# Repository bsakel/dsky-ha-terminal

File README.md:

# DSKY Home Assistant terminal

An Apollo Guidance Computer DSKY lookalike that works as a Home Assistant control terminal. It has:

- a **Raspberry Pi Zero 2 W** with a 4.0" 800×480 touch screen in the display window: a **FYSETC CTP40** (a HyperPixel 4.0 clone; the model and BOM still show the HyperPixel, see *Pending steps*);
- 19 **Gateron low-profile** keys;
- 10 RGB **status lights**, driven by an **RP2040-Zero** that appears to the Pi as a USB device.

The mechanical design is based on [MKme/AGC_DSKY_Replica](https://github.com/MKme/AGC_DSKY_Replica) (GPL-3.0). The main case and rear cover are dropped, the mid frame is split for support-free printing, and the electronics are new.

The STEP model of the original replica, with its lenses and original electronics, isn't in this repo. It's offered upstream instead, as `3D Models/DSKY_Original_Build.step`:

- the pull request: [MKme/AGC_DSKY_Replica#2](https://github.com/MKme/AGC_DSKY_Replica/pull/2), "Create a step file with the complete assembly";
- the fork it comes from: [bsakel/AGC_DSKY_Replica](https://github.com/bsakel/AGC_DSKY_Replica), [`3D Models/DSKY_Original_Build.step`](https://github.com/bsakel/AGC_DSKY_Replica/blob/master/3D%20Models/DSKY_Original_Build.step).

## Repository layout

```
hardware/
  BOM.md                    full bill of materials (printed parts, fasteners, electronics)
  cad/
    DSKY_HA_Terminal.step   this build: both options in one file as selectable components
                            (the original replica's STEP lives upstream, see above)
  pcb/                      Option A: KiCad projects, panel, JLCPCB BOM/CPL (see pcb/README.md)
  diy/                      Option B: hand-wired schematic (KiCad) + wiring diagram
firmware/                   RP2040-Zero firmware (keys + status lights)  - to do
software/                   Pi side: Home Assistant UI / bridge          - to do
docs/img/                   renders
```

## Two ways to build it

| | Option A – Custom PCBs | Option B – Hand-wired |
|---|---|---|
| Keys | Hot-swap sockets on a factory-assembled PCB | Switches wired point-to-point with 1N4148 diodes |
| Status lights | WS2812B on a PCB behind the splitter | 10 WS2812B mini boards in a printed holder |
| You solder | 19 sockets, RP2040-Zero, 2 connectors | Everything |
| Firmware | same | same |

Both options use the same matrix and pins, so one firmware covers both builds:

- **Rows:** GP28, GP29, GP15.
- **Columns:** GP9–GP13, GP26, GP27.
- **LED data:** GP14.

In `DSKY_HA_Terminal.step` the top-level components *Option A – Custom PCBs* and *Option B – Hand-wired* hold the parts that differ between the builds. Hide one of them in Fusion 360 to see the other build.

## Status

**Work in progress, parked.** The hardware is designed and passes KiCad DRC. Nothing has been ordered or built yet, and the firmware and software haven't been started.

- [x] 3D model (both options), printable parts, fasteners
- [x] PCBs designed, routed and panelised; JLCPCB BOM/CPL
- [x] Hand-wired schematic
- [x] KiCad DRC and ERC on both boards, the panel and the DIY schematic: no errors (warnings only, listed below)
- [ ] Footprint check against real parts, then order
- [ ] 3D model updated for the CTP40 screen and the final keyboard PCB
- [ ] Firmware
- [ ] Home Assistant software

## Pending steps

Work through these in order; each group builds on the one before.

### 1. PCBs (before ordering)

1. **Print the keyboard board 1:1** and lay a real Gateron LP switch, hot-swap socket and RP2040-Zero on it.
2. **Gateron_LP_Hotswap footprint.** Its back-side courtyard (x −9.75…8.0, y 2.0…8.3) was estimated from the pad positions. Check it against the socket datasheet.
3. **RP2040-Zero footprint.** The copy on the keyboard board differs from the one in `lib/dsky.pretty`. Compare both with the Waveshare drawing, then keep the correct one in both places.
4. **3D viewer (Alt+3)** in KiCad: check that the sockets and RP2040 sit on the back and the LEDs on the front.
5. **Optional clean-ups** (all DRC warnings, none block ordering):
   - Net names differ between schematic and board (`/+5V` vs `+5V`, 235 parity warnings). It comes from the generator's labels; "Update PCB from schematic" would rename every net.
   - Add no-connect flags to the unused RP2040 pins and the last LED's DOUT (the ERC errors).
   - Silkscreen overlaps and clipping, the missing `MPN` field, `MouseBite_0.5` missing from the library.
6. **Order.** Follow `hardware/pcb/README.md`: Gerbers plus the BOM/CPL files from `pcb/jlcpcb/panel/`. Check the rotation of every part in JLCPCB's placement preview (WS2812B notch, diode bands).

### 2. Mechanical (3D model, in Fusion 360)

1. **Swap the HyperPixel for the CTP40** ([FYSETC/FYSETC-CTP40](https://github.com/FYSETC/FYSETC-CTP40)):
   - The CTP40's active area sits about 1.5 mm further along the long axis than the HyperPixel's, relative to the mounting holes. Move the two display-housing holes by that much (confirm against the FYSETC drawing first).
   - The CTP40's thickness isn't published. Measure it; the model allows 4.0 mm from the back of the board to the front of the glass.
   - Rename the "(HyperPixel)" parts here and in `hardware/BOM.md`.
2. **Keyboard PCB model:** update it to the KiCad board. It still has the old MX-style holes and lacks the RP2040 tab.
3. **Spacers:** the keyboard spacers are Ø6.5 mm. The PCB courtyards now allow for that (r 3.5 on the back), so keep them that size or smaller.
4. **Upstream PR.** Follow up on [MKme/AGC_DSKY_Replica#2](https://github.com/MKme/AGC_DSKY_Replica/pull/2), the original-build STEP file. Once it's merged, point the links above at MKme's repo instead of the fork.
5. Export the STLs (see `hardware/BOM.md`).

### 3. Firmware (RP2040-Zero)

Decisions to make first, one at a time:

1. **Stack:** CircuitPython, MicroPython, Arduino-Pico or KMK/QMK.
2. **Pi ↔ RP2040 protocol:** USB CDC serial, HID + serial, or something else. Key events go up to the Pi; lamp states come down.
3. **LED brightness limit:** all 10 LEDs at full white draw about 600 mA from the Pi's USB port, so the firmware must cap it.

Pins, matrix and LED order are in `firmware/README.md`.

### 4. Software (Pi Zero 2 W)

1. **CTP40 driver:** FYSETC ships Pi 3/Pi 4 overlays. Check what works on the current Raspberry Pi OS on the Zero 2 W.
2. **UI:** a kiosk browser (for example a Home Assistant dashboard) or a native app.
3. **VERB/NOUN mapping:** design how DSKY-style VERB/NOUN entries map to Home Assistant services.

### Notes for picking this up again

- **KiCad version.** The projects are KiCad 8 format. KiCad 10 opens them, but saving converts the files to the new format. Decide whether to upgrade before you edit and save in KiCad 10.
- **Generators.** `hardware/pcb/scripts/` generates the boards. Regenerating overwrites every hand edit, so prefer small targeted patches.
- **Python.** Python isn't on the PATH on the dev machine. KiCad's bundled Python works (it includes numpy): `"C:\Program Files\KiCad\10.0\bin\python.exe"`.
- **DRC from the command line.** This runs without saving the board:

  ```bash
  kicad-cli pcb drc --refill-zones --schematic-parity --severity-all -o drc.rpt hardware/pcb/keyboard-board/keyboard_board.kicad_pcb
  ```

  Use the same command for the status board, and drop `--schematic-parity` for the panel.

## Licence

GPL-3.0, inherited from the original AGC_DSKY_Replica project. See `LICENSE`.

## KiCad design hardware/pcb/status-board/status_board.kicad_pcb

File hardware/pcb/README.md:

# Custom PCBs (Option A)

| Folder | What it is |
|---|---|
| `keyboard-board/` | 168 × 77 mm board with 19 Gateron LP hot-swap sockets, a diode per key and the RP2040-Zero on the back. |
| `status-board/` | 60 × 106 mm board with 10 WS2812B LEDs behind the status lenses. |
| `panel/` | Both boards in one 230 × 106 mm panel joined by two mouse-bite tabs. This is the file you order. |
| `lib/` | Project symbol and footprint libraries, used by all three projects through `${KIPRJMOD}/../lib`. |
| `jlcpcb/` | BOM and CPL (pick-and-place) files for JLCPCB assembly, one set per project. |
| `scripts/` | The Python generators that produced the boards. Only needed if you want to regenerate them. |

Both boards were routed and checked with the generator's own clearance and connectivity checks:

- 0.2 mm copper clearance and 0.4 mm to the board edge.
- No errors and no unconnected nets.

KiCad's DRC is still the final word.

## Before ordering (KiCad 8)

1. **Check the footprints against real parts.**
   - Open `lib/dsky.pretty` in the footprint editor.
   - **Gateron_LP_Hotswap.** Check it against your socket's datasheet: the centre hole is 5.1 mm, the two pin holes are 3.0 mm, and the pads are on the back. Print the board 1:1 on paper and lay a switch on it.
   - **RP2040-Zero.** Check the pad pitch and pin names against the Waveshare drawing. The module is soldered to the back by its castellated edge, with the USB-C pointing up out of the tab.
2. **Open each board.** Open `keyboard-board/keyboard_board.kicad_pro` and `status-board/status_board.kicad_pro`.
   - Press **B** to fill the zones. The GND pour on the back layer is defined but not filled.
   - Run **Inspect → Design Rules Checker** with *Test for parity between PCB and schematic* enabled.
   - Fix or accept anything it reports. Silkscreen-over-pad warnings are cosmetic.
3. **Open the panel.** Open `panel/dsky_panel.kicad_pcb`, fill the zones (B) and run DRC.
   - The panel has no schematic, so turn off schematic parity.
   - Nets carry a `K_` prefix (keyboard) or `S_` prefix (status), and status-board references are numbered from 100 so that they don't clash.
4. **Make the Gerbers.** Use *File → Fabrication Outputs → Gerbers* with JLCPCB's recommended settings, plus the drill files. Alternatively, install the **Fabrication Toolkit** plugin, which builds Gerbers, BOM and CPL in one click.
5. **Upload to JLCPCB.**
   - Board settings: 2 layers, 1.6 mm, HASL lead-free or ENIG, any colour.
   - **Assembly:** PCBA, top side. Upload `jlcpcb/panel/dsky_panel_BOM.csv` and `dsky_panel_CPL.csv`.
   - In the placement preview, **check the rotation of every part type**, especially the WS2812B LEDs: the notch (pin 1, VDD) must sit at the marked corner. The diode band must face the cathode mark. Rotate any part that is off in the preview; JLC applies your correction.
   - The hot-swap sockets, RP2040-Zero and connectors are marked *do not populate*. They are deliberately missing from the BOM, so JLC will not ask about them.

## Panel or separate boards?

JLCPCB treats a file containing several designs as a panel and may add a small "multiple designs" fee. Compare two quotes:

1. **The panel.** One board of 230 × 106 mm and one assembly setup.
2. **Two separate orders.** Two boards under 100 × 100 / 170 mm and two setups.

Assembly setup and extended-part fees usually make the panel the cheaper option. If they don't, the individual projects are ready to order on their own with their own BOM/CPL.

After delivery, snap the panel apart at the two mouse-bite tabs (pliers, then file the nubs flat).

## Hand assembly after delivery

1. **Hot-swap sockets** (back side): 19 of them, two pads each. Tin one pad, place the socket, then solder both pads.
2. **RP2040-Zero** (back side): line up the castellations with the pads and solder only the pins that are used. Those are 5V, GND, GP9–GP15 and GP26–GP29; soldering all of them is fine too.
3. **Status cable**, between J1 on the keyboard board and J101 (J1 on its own board) on the status board:
   - Pin 1: +5V
   - Pin 2: DIN
   - Pin 3: GND

## Pin map (same for both builds)

| Function | RP2040 GPIO |
|---|---|
| ROW0 (VERB, +, 7, 8, 9, CLR, ENTR) | GP28 |
| ROW1 (NOUN, −, 4, 5, 6, PRO, RSET) | GP29 |
| ROW2 (0, 1, 2, 3, KEY REL) | GP15 |
| COL0 … COL6 | GP9, GP10, GP11, GP12, GP13, GP26, GP27 |
| WS2812B data | GP14 (buffered to 5 V on Option A) |

The diodes go column → row (COL2ROW).

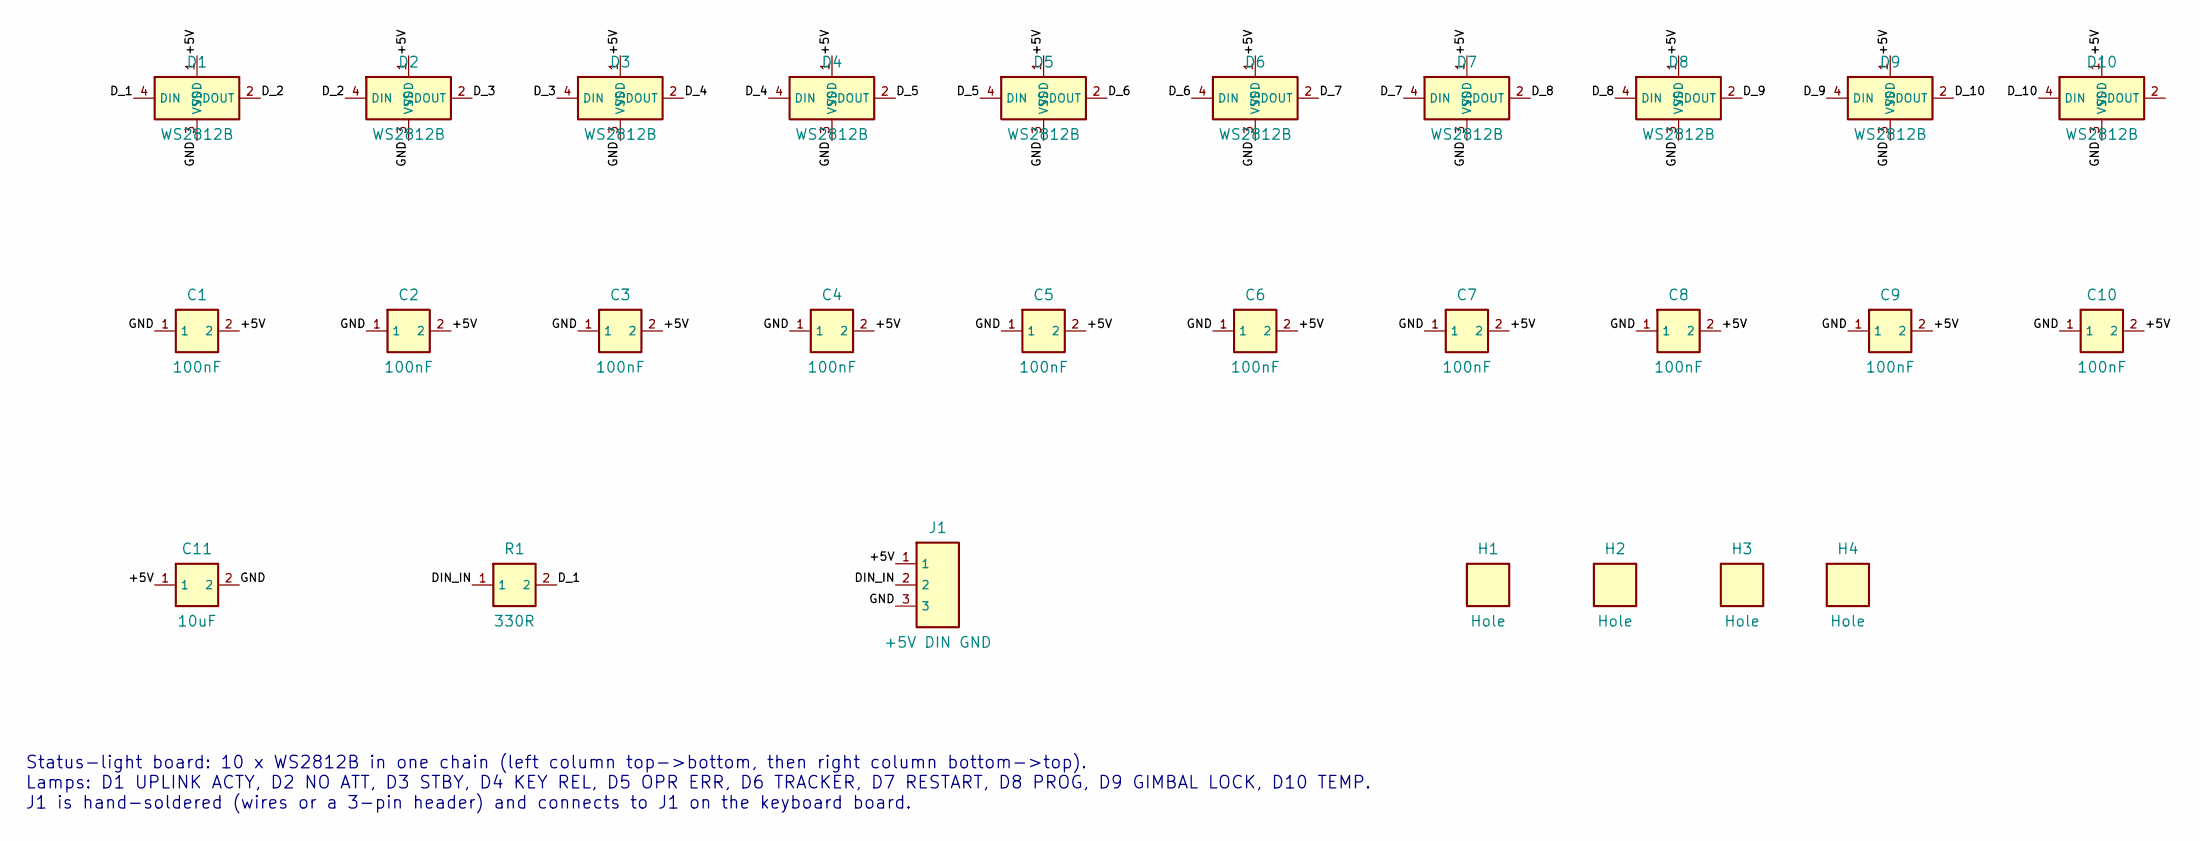
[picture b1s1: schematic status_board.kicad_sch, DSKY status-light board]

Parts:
C1, C2, C3, C4, C5, C6, C7, C8, C9, C10: 100nF; C_0603; MPN CC0603KRX7R9BB104; LCSC C14663
C11: 10uF; C_0805; MPN CL21A106KAYNNNE; LCSC C15850
D1, D2, D3, D4, D5, D6, D7, D8, D9, D10: WS2812B; WS2812B_5050; MPN WS2812B-B/T; LCSC C2761795
H1, H2, H3, H4: Hole; Hole_2.2
J1: +5V DIN GND; Conn_1x03_P2.54
R1: 330R; R_0603; MPN 0603WAF3300T5E; LCSC C23138

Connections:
+5V: C1.2, C2.2, C3.2, C4.2, C5.2, C6.2, C7.2, C8.2, C9.2, C10.2, C11.1, D1.1 (VDD), D2.1 (VDD), D3.1 (VDD), D4.1 (VDD), D5.1 (VDD), D6.1 (VDD), D7.1 (VDD), D8.1 (VDD), D9.1 (VDD), D10.1 (VDD), J1.1
DIN_IN: J1.2, R1.1
D_1: D1.4 (DIN), R1.2
D_2: D1.2 (DOUT), D2.4 (DIN)
D_3: D2.2 (DOUT), D3.4 (DIN)
D_4: D3.2 (DOUT), D4.4 (DIN)
D_5: D4.2 (DOUT), D5.4 (DIN)
D_6: D5.2 (DOUT), D6.4 (DIN)
D_7: D6.2 (DOUT), D7.4 (DIN)
D_8: D7.2 (DOUT), D8.4 (DIN)
D_9: D8.2 (DOUT), D9.4 (DIN)
D_10: D9.2 (DOUT), D10.4 (DIN)
GND: C1.1, C2.1, C3.1, C4.1, C5.1, C6.1, C7.1, C8.1, C9.1, C10.1, C11.2, D1.3 (VSS), D2.3 (VSS), D3.3 (VSS), D4.3 (VSS), D5.3 (VSS), D6.3 (VSS), D7.3 (VSS), D8.3 (VSS), D9.3 (VSS), D10.3 (VSS), J1.3

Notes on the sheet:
Status-light board: 10 x WS2812B in one chain (left column top->bottom, then right column bottom->top). Lamps: D1 UPLINK ACTY, D2 NO ATT, D3 STBY, D4 KEY REL, D5 OPR ERR, D6 TRACKER, D7 RESTART, D8 PROG, D9 GIMBAL LOCK, D10 TEMP. J1 is hand-soldered (wires or a 3-pin header) and connects to J1 on t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

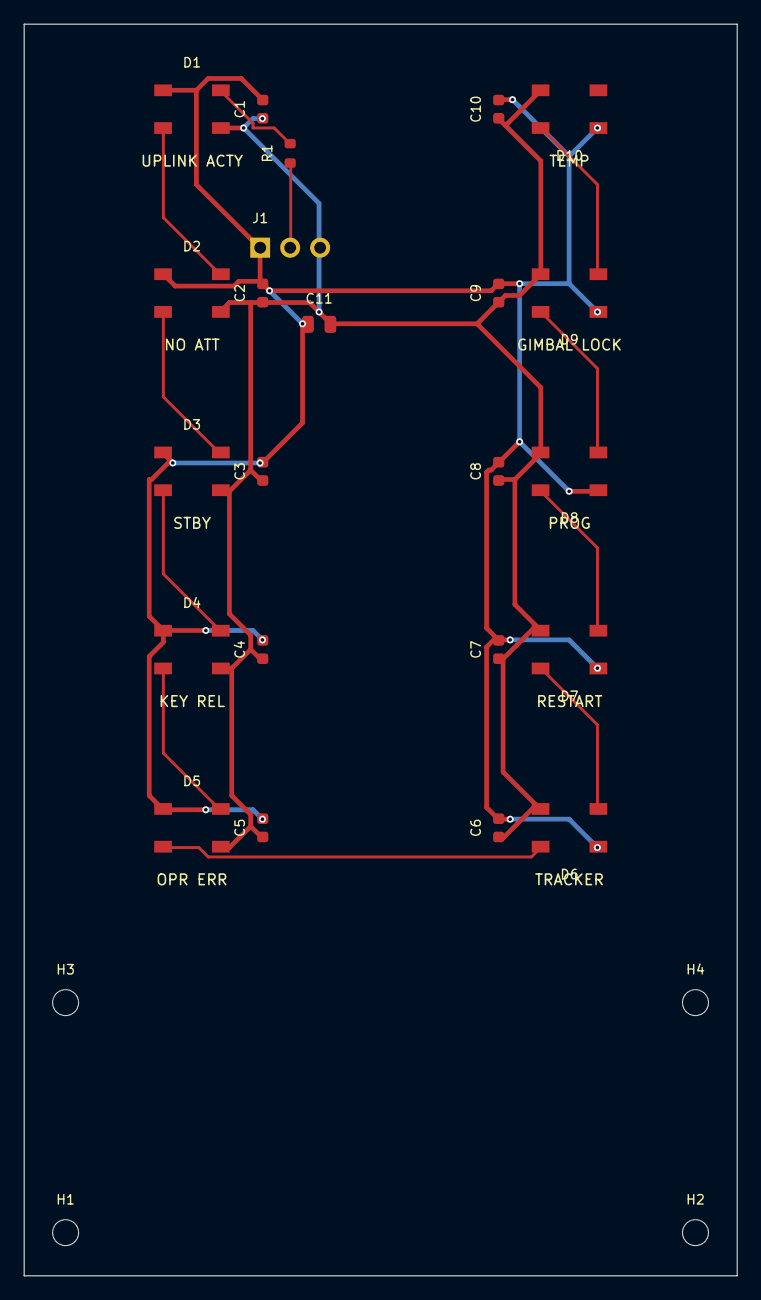
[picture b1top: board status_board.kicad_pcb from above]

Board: 2 copper layers, 60.5 x 106.1 mm, 27 parts (0 on the bottom side), 13 nets.

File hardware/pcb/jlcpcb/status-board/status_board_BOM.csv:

Comment,Designator,Footprint,JLCPCB Part #
100nF,"C1,C2,C3,C4,C5,C6,C7,C8,C9,C10",C_0603,C14663
10uF,C11,C_0805,C15850
330R,R1,R_0603,C23138
WS2812B,"D1,D2,D3,D4,D5,D6,D7,D8,D9,D10",WS2812B_5050,C2761795

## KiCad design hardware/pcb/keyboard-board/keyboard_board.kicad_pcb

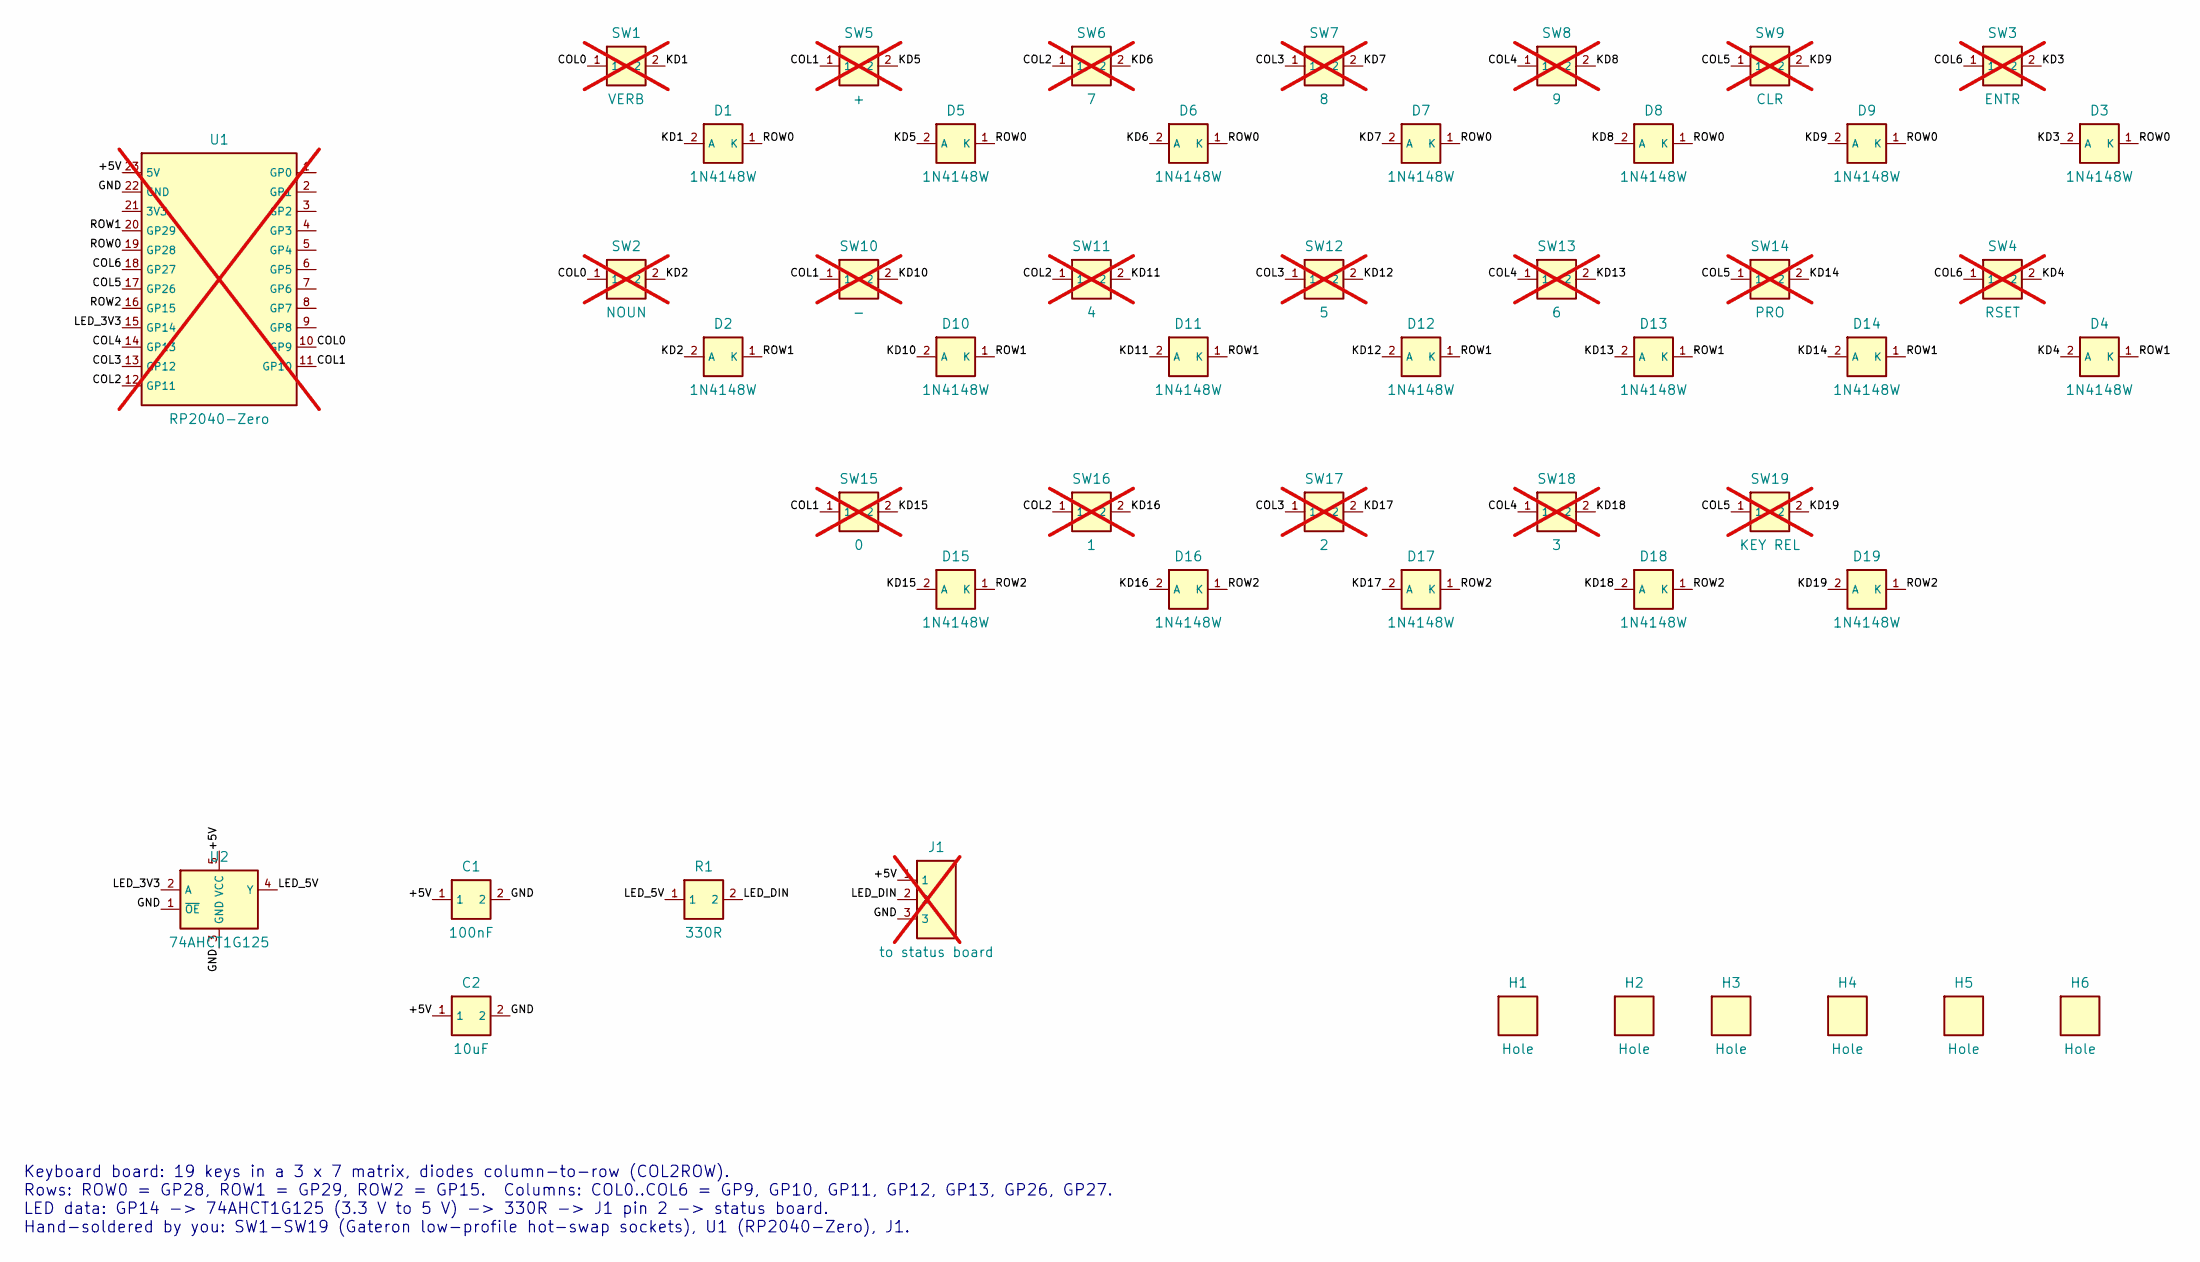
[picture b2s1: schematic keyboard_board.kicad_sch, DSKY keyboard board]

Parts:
C1: 100nF; C_0603; MPN CC0603KRX7R9BB104; LCSC C14663
C2: 10uF; C_0805; MPN CL21A106KAYNNNE; LCSC C15850
D1, D2, D3, D4, D5, D6, D7, D8, D9, D10, D11, D12, D13, D14, D15, D16, D17, D18, D19: 1N4148W; D_SOD-123; MPN 1N4148W; LCSC C81598
H1, H2, H3, H4, H5, H6: Hole; MountingHole_M3
J1: to status board; Conn_1x03_P2.54; not fitted
R1: 330R; R_0603; MPN 0603WAF3300T5E; LCSC C23138
SW1: VERB; Gateron_LP_Hotswap; not fitted
SW2: NOUN; Gateron_LP_Hotswap; not fitted
SW3: ENTR; Gateron_LP_Hotswap; not fitted
SW4: RSET; Gateron_LP_Hotswap; not fitted
SW5: +; Gateron_LP_Hotswap; not fitted
SW6: 7; Gateron_LP_Hotswap; not fitted
SW7: 8; Gateron_LP_Hotswap; not fitted
SW8: 9; Gateron_LP_Hotswap; not fitted
SW9: CLR; Gateron_LP_Hotswap; not fitted
SW10: -; Gateron_LP_Hotswap; not fitted
SW11: 4; Gateron_LP_Hotswap; not fitted
SW12: 5; Gateron_LP_Hotswap; not fitted
SW13: 6; Gateron_LP_Hotswap; not fitted
SW14: PRO; Gateron_LP_Hotswap; not fitted
SW15: 0; Gateron_LP_Hotswap; not fitted
SW16: 1; Gateron_LP_Hotswap; not fitted
SW17: 2; Gateron_LP_Hotswap; not fitted
SW18: 3; Gateron_LP_Hotswap; not fitted
SW19: KEY REL; Gateron_LP_Hotswap; not fitted
U1: RP2040-Zero; not fitted
U2: 74AHCT1G125; SOT-23-5; MPN SN74AHCT1G125DBVR; LCSC C7484

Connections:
+5V: C1.1, C2.1, J1.1, U1.23 (5V), U2.5 (VCC)
COL0: SW1.1, SW2.1, U1.10 (GP9)
COL1: SW5.1, SW10.1, SW15.1, U1.11 (GP10)
COL2: SW6.1, SW11.1, SW16.1, U1.12 (GP11)
COL3: SW7.1, SW12.1, SW17.1, U1.13 (GP12)
COL4: SW8.1, SW13.1, SW18.1, U1.14 (GP13)
COL5: SW9.1, SW14.1, SW19.1, U1.17 (GP26)
COL6: SW3.1, SW4.1, U1.18 (GP27)
GND: C1.2, C2.2, J1.3, U1.22 (GND), U2.1 (~OE), U2.3 (GND)
KD1: D1.2 (A), SW1.2
KD2: D2.2 (A), SW2.2
KD3: D3.2 (A), SW3.2
KD4: D4.2 (A), SW4.2
KD5: D5.2 (A), SW5.2
KD6: D6.2 (A), SW6.2
KD7: D7.2 (A), SW7.2
KD8: D8.2 (A), SW8.2
KD9: D9.2 (A), SW9.2
KD10: D10.2 (A), SW10.2
KD11: D11.2 (A), SW11.2
KD12: D12.2 (A), SW12.2
KD13: D13.2 (A), SW13.2
KD14: D14.2 (A), SW14.2
KD15: D15.2 (A), SW15.2
KD16: D16.2 (A), SW16.2
KD17: D17.2 (A), SW17.2
KD18: D18.2 (A), SW18.2
KD19: D19.2 (A), SW19.2
LED_3V3: U1.15 (GP14), U2.2 (A)
LED_5V: R1.1, U2.4 (Y)
LED_DIN: J1.2, R1.2
ROW0: D1.1 (K), D3.1 (K), D5.1 (K), D6.1 (K), D7.1 (K), D8.1 (K), D9.1 (K), U1.19 (GP28)
ROW1: D2.1 (K), D4.1 (K), D10.1 (K), D11.1 (K), D12.1 (K), D13.1 (K), D14.1 (K), U1.20 (GP29)
ROW2: D15.1 (K), D16.1 (K), D17.1 (K), D18.1 (K), D19.1 (K), U1.16 (GP15)

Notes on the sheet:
Keyboard board: 19 keys in a 3 x 7 matrix, diodes column-to-row (COL2ROW). Rows: ROW0 = GP28, ROW1 = GP29, ROW2 = GP15. Columns: COL0..COL6 = GP9, GP10, GP11, GP12, GP13, GP26, GP27. LED data: GP14 -> 74AHCT1G125 (3.3 V to 5 V) -> 330R -> J1 pin 2 -> status board. Hand-soldered by you: SW1-SW19 (Ga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

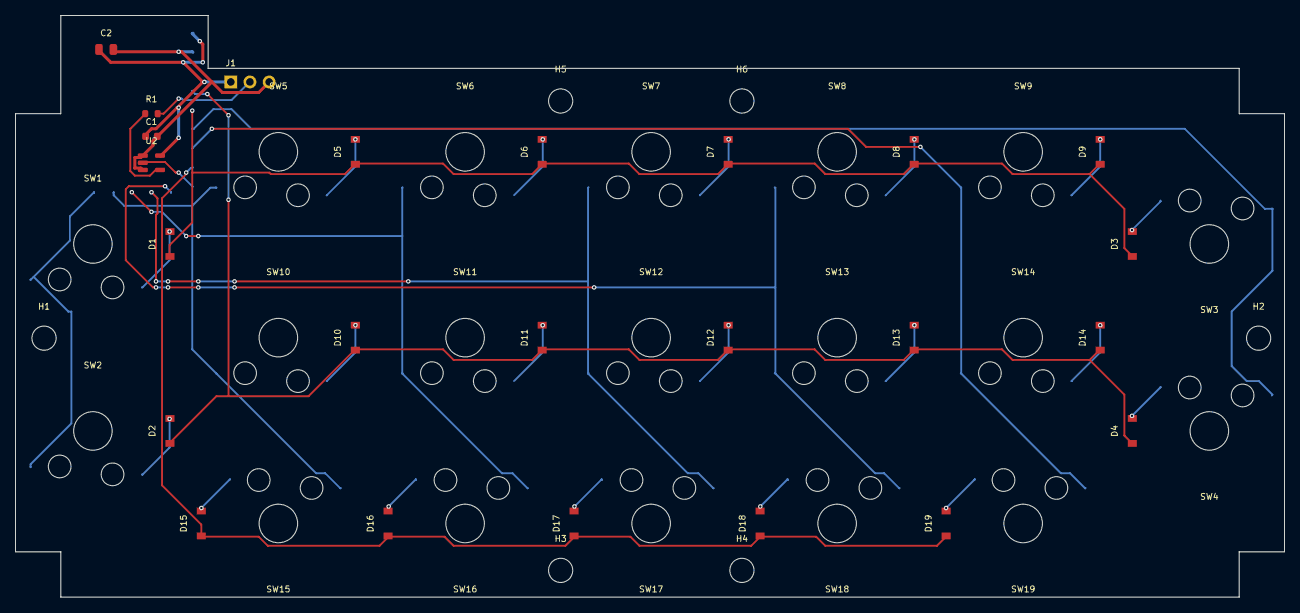
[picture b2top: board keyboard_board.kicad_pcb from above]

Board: 2 copper layers, 168.0 x 77.0 mm, 50 parts (1 on the bottom side), 34 nets.
